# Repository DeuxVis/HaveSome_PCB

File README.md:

## Intro

This is a breakout board for low pin count SMD components : 0402 0603 0805 1206 SOT23 SOT223 SOT323.

Before that when you wanted to breadboard some SMD components it was a bit tricky :

Now you can use those tiny pretty easy to solder adapters :

## Example uses

See some [sample usages](https://hackaday.io/project/10412-hacker-breakout-board-for-most-popular-smd#menu-details)

## Motivation

This breakout board is usefull to prototype with SMD components by allowing to plug those in a breadboard - or any matching 0.1" spaced pins, like some arduino family boards for instance.

It is derived from the [Awesome PCB project](https://hackaday.io/project/10412-hacker-breakout-board-for-most-popular-smd) by Simon.

My motivation for redesigning it from scratch was to :

*   Learn Kicad.
*   Allow people to order those boards for themselves, as Simon did not "yet" release his files.
*   I need to use some of those.

## Documentation

Not much yet, some pictures in the Doc subfolder.
You can probably use some informations in the [pdf from awesomepcb](http://www.awesomepcb.com/wp-content/uploads/2015/06/0603_0805_1206_SOT23_SOT223_0402_SOT323_rev01_documentation-PCB.pdf) although that board is somewhat different.

## Changelog

### V1.1

Status : still untested.

* Trying to let PCBs.io manufacturing process actually produce vias by not burying them under a pad.
* Beefier traces, especially on center pin - thanks to original Awsome PCB designer Simon for the suggestion on hackaday.io.
* Beefier vias for better current/heat transfer.
* Linked pad 2 and 4 of SOT223 for footprint compatible packages which lack the middle pin. 
* Added silkscreen annotations of pads to pins id matching - thanks to warhawk-avg on hackaday.io for the suggestion.

### V1.0

Status : tested and working but might be bugged depending on PCB manufacturer, vias between top and bottom heatsink surface may not be produced.

## License

This work is licensed under a [Creative Commons Attribution-NonCommercial-ShareAlike 3.0 Unported](https://creativecommons.org/licenses/by-nc-sa/3.0/) License - aka CC BY-NC-SA 3.0.

I chose non commercial because the idea is not mine and I don't want someone ripping off sales from [the original publisher](http://www.awesomepcb.com/product-category/pcb-bread-board-tools/).

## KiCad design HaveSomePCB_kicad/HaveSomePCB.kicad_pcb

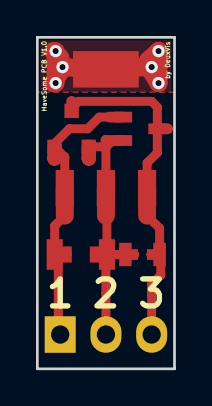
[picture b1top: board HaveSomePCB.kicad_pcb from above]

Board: 2 copper layers, 7.6 x 18.4 mm, 8 parts (0 on the bottom side), 3 nets.

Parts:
PINS1: CONN_01X03; Pin_Header_Straight_1x03
SMD402: R0402; R_0402
SMD603: R0603; R_0603
SMD805: R0805; R_0805
SMD1206: R1206; R_1206
SOT23: APE8865NL-33-HF-3; SOT-23
SOT223: LD1117S33CTR; SOT-223
SOT323: BFR92; SOT-323

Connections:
unnamed: PINS1.1, SMD603.2, SMD1206.2, SOT23.1, SOT223.1, SOT323.1
unnamed: PINS1.2, SMD402.2, SMD603.1, SMD805.2, SMD1206.1, SOT23.2, SOT223.2, SOT323.2
unnamed: PINS1.3, SMD402.1, SMD805.1, SOT23.3, SOT223.3, SOT323.3

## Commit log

2016-08-04 First import commit.
2016-08-04 Licensing information updated.
2016-08-04 Bah ! damn irregular verbs.
2016-08-18 Photos of the boards fabricated.
2016-10-25 Giving pictures some meaning.
2016-10-25 Thumbnails for web display.
2016-10-25 Doc Update.
2016-10-25 Typo fix.
2017-01-18 Version 1.1 : - Trying to let PCBs.io manufacturing process actually produce vias by not burying them under a pad. - Beefier traces, especially on center pin - thanks to original Awsome PCB designer 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
2017-01-18 Updating readme for 1.1 version.
2017-01-18 Removed duplicated file from gerbers zip.
